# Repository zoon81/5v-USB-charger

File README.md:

# 5v-USB-charger
Redesigned DC/DC converter for "MULTI SOCKET CAR CIGARETTE LIGHTER With USB Port"
Improved DC/DC converter for my MULTI SOCKET CAR CIGARETTE LIGHTER.

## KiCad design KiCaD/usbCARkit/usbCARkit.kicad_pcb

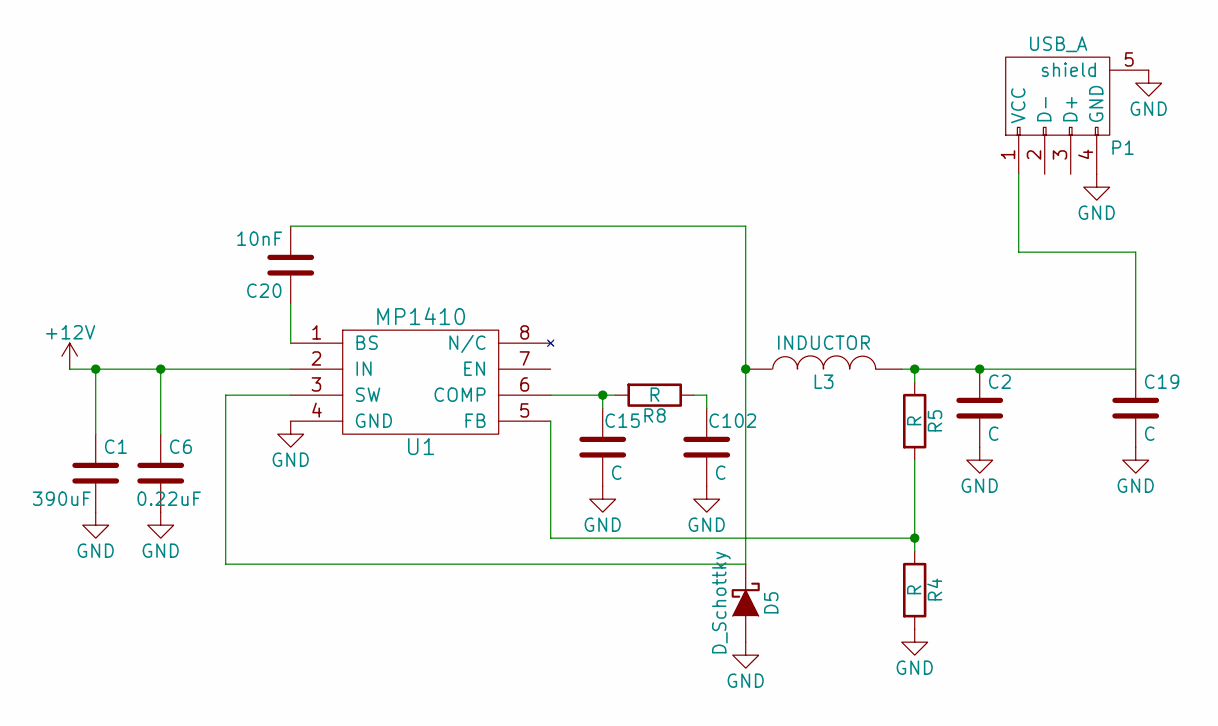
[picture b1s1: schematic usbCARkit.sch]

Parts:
C1: 390uF; Elko_vert_11.5x8mm_RM3.5
C2, C15, C102: C; C_0805
C6: 0.22uF; C_0805
C19: C; Elko_vert_11.5x8mm_RM3.5
C20: 10nF; C_0805
D5: D_Schottky; Diode-SMC_Standard
L3: INDUCTOR; SELF-WE-PD-XXL
P1: USB_A
R4, R5, R8: R; R_0805
U1: MP1410; SOIC-8_3.9x4.9mm_Pitch1.27mm

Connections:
+12V: C1.1, C6.1, U1.2 (IN)
GND: C1.2, C2.2, C6.2, C15.2, C19.2, C102.2, D5.2 (A), P1.4 (GND), P1.5 (shield), R4.2, U1.4 (GND)
unnamed: C15.1, R8.2, U1.6 (COMP)
unnamed: C2.1, C19.1, L3.2, P1.1 (VCC), R5.1
unnamed: C20.1, U1.1 (BS)
unnamed: C20.2, D5.1 (K), L3.1, U1.3 (SW)
unnamed: C102.1, R8.1
unnamed: R4.1, R5.2, U1.5 (FB)

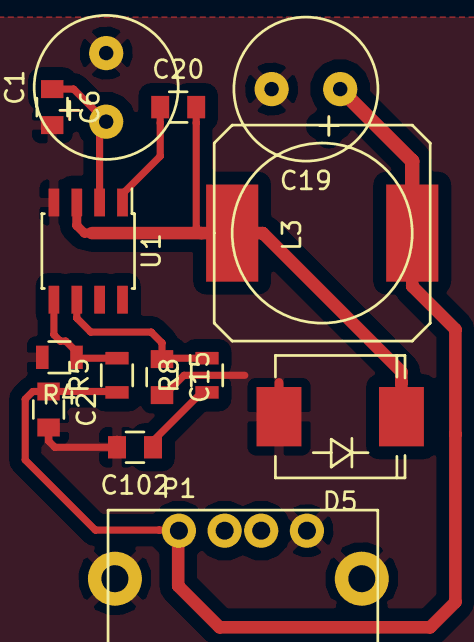
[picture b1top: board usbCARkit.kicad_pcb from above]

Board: 2 copper layers, 14 parts (0 on the bottom side), 8 nets.
